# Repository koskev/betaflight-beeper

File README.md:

# bf-beeper

This is a small beeper board, which is designed to find a lost model aircraft.
It functions pretty much identical to the other commercial beepers.
The main feature is the ability to deactivate the beeper using Betaflight.

Just activate the normal beeper function of Betaflight and pull the battery.
Since the manual beep pattern is unique all other beep sources won't trigger the disarm.

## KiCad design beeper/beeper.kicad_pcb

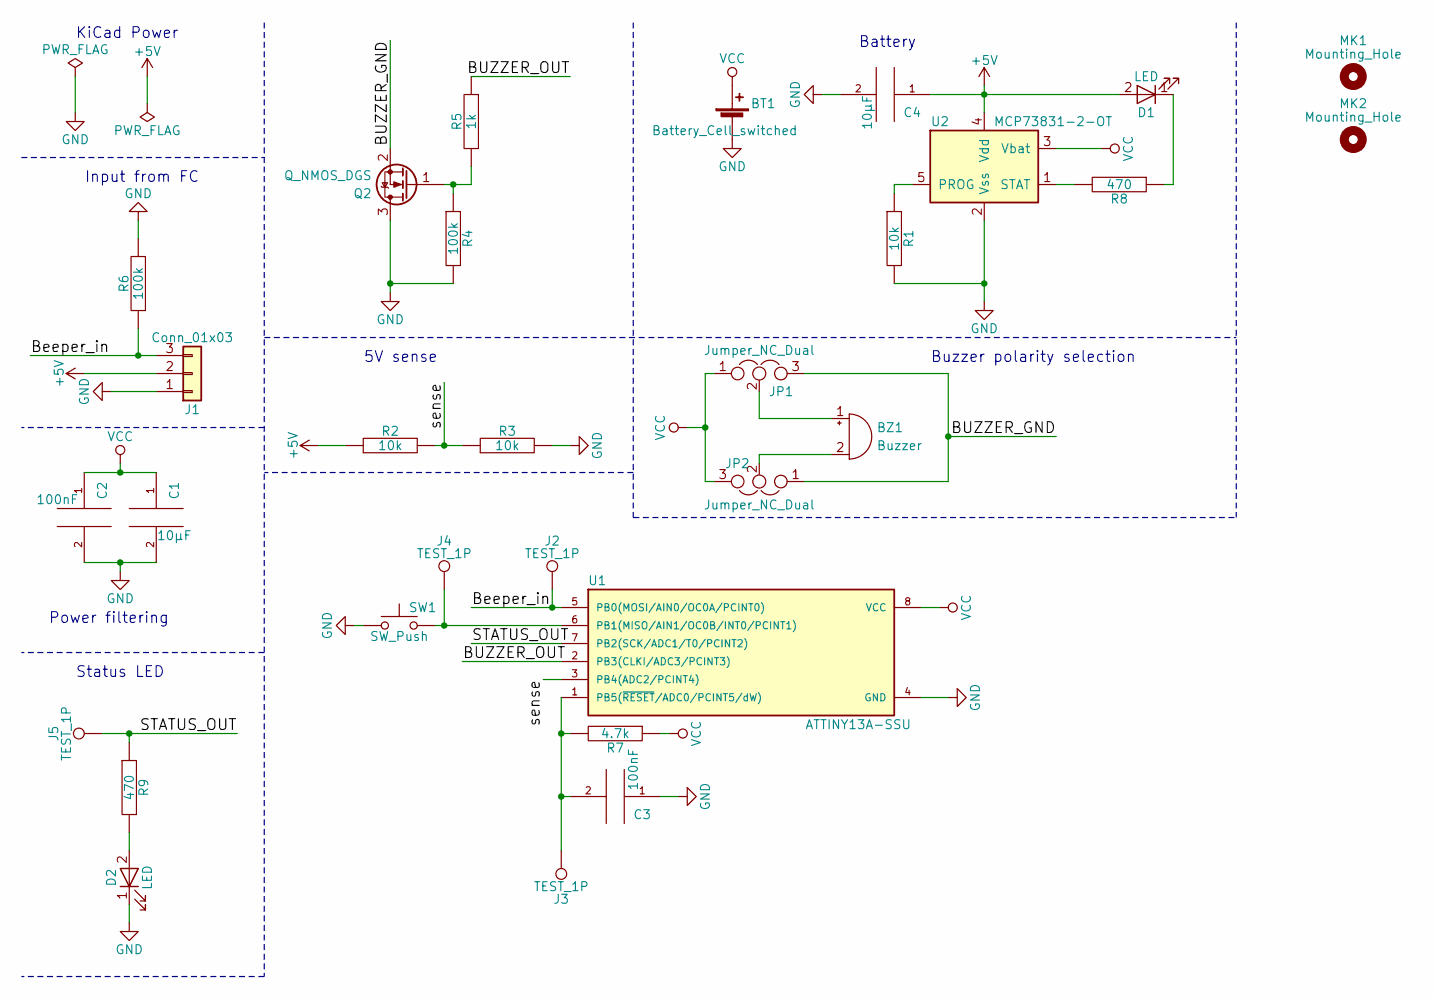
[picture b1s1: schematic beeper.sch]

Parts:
BT1: Battery_Cell_switched; PinHeader_2x01_P1.00mm_Vertical_SMD
BZ1: Buzzer; Buzzer_12x9.5RM7.6
C1, C4: 10µF; C_0805_2012Metric
C2, C3: 100nF; C_0603_1608Metric
D1, D2: LED; LED_0805_2012Metric_Castellated
J1: Conn_01x03; PinHeader_1x03_P2.54mm_Vertical
J2, J3, J4, J5: TEST_1P; TestPoint_Pad_D1.0mm
JP1, JP2: Jumper_NC_Dual; SolderJumper-3_P1.3mm_Open_RoundedPad1.0x1.5mm
MK1, MK2: Mounting_Hole; MountingHole_3.2mm_M3
Q2: Q_NMOS_DGS; SOT-23
R1, R2, R3: 10k; R_0805_2012Metric
R4, R6: 100k; R_0805_2012Metric
R5: 1k; R_0805_2012Metric
R7: 4.7k; R_0805_2012Metric
R8, R9: 470; R_0805_2012Metric
SW1: SW_Push; SW_SPST_CK_RS282G05A3
U1: ATTINY13A-SSU; SOIC-8_3.9x4.9mm_P1.27mm
U2: MCP73831-2-OT; SOT-23-5

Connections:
+5V: C4.1, D1.2 (A), J1.2, R2.1, U2.4 (Vdd)
/BUZZER_GND: JP1.3, JP2.1, Q2.2 (S)
/BUZZER_OUT: R5.2, U1.2 (PB3(CLKI/ADC3/PCINT3))
/Beeper_in: J1.3, J2.1, R6.1, U1.5 (PB0(MOSI/AIN0/OC0A/PCINT0))
/STATUS_OUT: J5.1, R9.1, U1.7 (PB2(SCK/ADC1/T0/PCINT2))
/sense: R2.2, R3.1, U1.3 (PB4(ADC2/PCINT4))
GND: BT1.1 (-), C1.2, C2.2, C3.1, C4.2, D2.1 (K), J1.1, Q2.3 (D), R1.2, R3.2, R4.2, R6.2, SW1.1, U1.4 (GND), U2.2 (Vss)
unnamed: BZ1.1 (-), JP1.2
unnamed: BZ1.2 (+), JP2.2
unnamed: C3.2, J3.1, R7.2, U1.1 (PB5(~RESET~/ADC0/PCINT5/dW))
unnamed: D1.1 (K), R8.1
unnamed: D2.2 (A), R9.2
unnamed: J4.1, SW1.2, U1.6 (PB1(MISO/AIN1/OC0B/INT0/PCINT1))
unnamed: Q2.1 (G), R4.1, R5.1
unnamed: R1.1, U2.5 (PROG)
unnamed: R8.2, U2.1 (STAT)
VCC: BT1.2 (+), C1.1, C2.1, JP1.1, JP2.3, R7.1, U1.8 (VCC), U2.3 (Vbat)

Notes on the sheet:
KiCad Power
Input from FC
Battery
Power filtering
5V sense
Status LED
Buzzer polarity selection

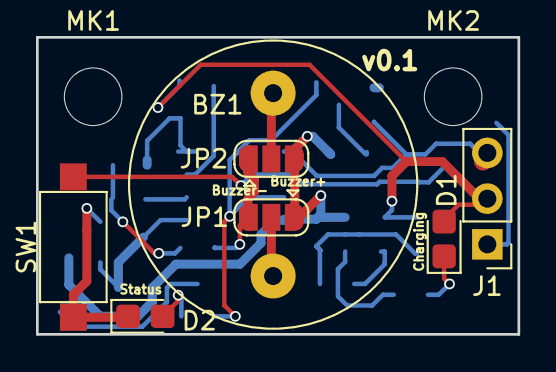
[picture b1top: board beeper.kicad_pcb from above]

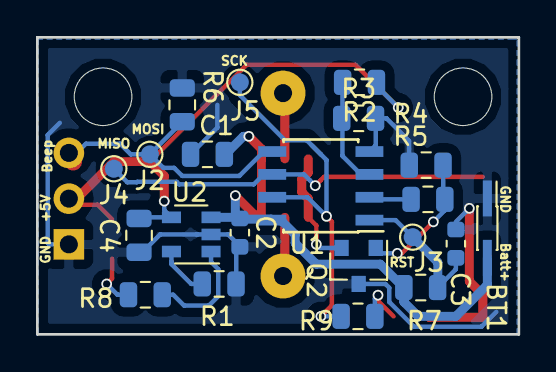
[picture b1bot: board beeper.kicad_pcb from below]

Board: 2 copper layers, 26.8 x 16.5 mm, 30 parts (21 on the bottom side), 17 nets.

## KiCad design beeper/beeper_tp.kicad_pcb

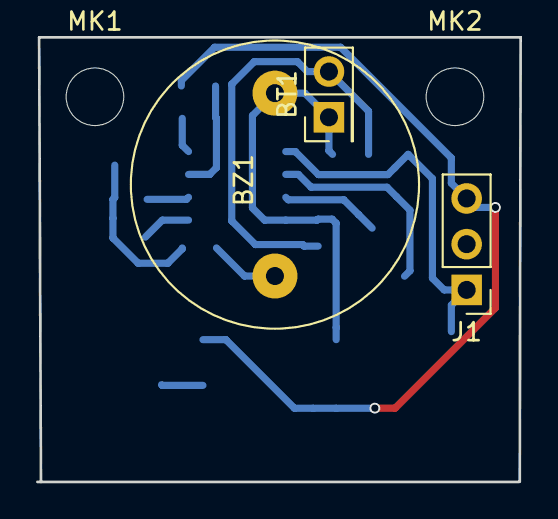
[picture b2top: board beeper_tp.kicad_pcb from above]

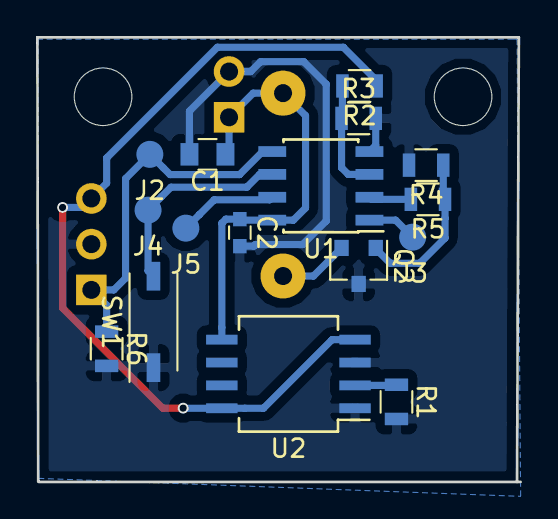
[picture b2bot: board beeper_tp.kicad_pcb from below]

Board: 2 copper layers, 26.8 x 24.7 mm, 21 parts (16 on the bottom side), 12 nets.

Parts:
BT1: Battery_Cell; Pin_Header_Straight_2x01_Pitch2.54mm
BZ1: Buzzer; BUZZER
C1: 10µF; C_0805
C2: 100nF; C_0603
J1: Conn_01x03; Pin_Header_Straight_1x03_Pitch2.54mm
J2, J3, J4, J5: TEST_1P; Measurement_Point_Round-SMD-Pad_Small
MK1, MK2: Mounting_Hole; MountingHole_3.2mm_M3
Q2: Q_NMOS_DGS; SOT-23
R1, R2, R3, R4, R5, R6: R; R_0805
SW1: SW_Push; SW_DIP_x1_W5.08mm_Slide_Copal_CHS-A
U1: ATTINY13A-SSU; SOIC-8_3.9x4.9mm_Pitch1.27mm
U2: TP4056; SO-8_5.3x6.2mm_Pitch1.27mm

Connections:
+5V: J1.3, R2.1, U2.4, U2.8
/Beeper_in: J1.1, J2.1, R6.1, U1.5
/sense: R2.2, R3.1, U1.3
GND: BT1.2, C1.2, C2.2, J1.2, Q2.3, R1.2, R3.2, R4.2, R6.2, SW1.1, U1.4, U2.1, U2.3
unnamed: BZ1.1, Q2.2
unnamed: J3.1, U1.1
unnamed: J4.1, SW1.2, U1.6
unnamed: J5.1, U1.7
unnamed: Q2.1, R4.1, R5.1
unnamed: R1.1, U2.2
unnamed: R5.2, U1.2
VCC: BT1.1, BZ1.2, C1.1, C2.1, U1.8, U2.5

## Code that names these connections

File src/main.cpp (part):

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
#define SENSE_DDR DDRB
#define SENSE_PORT PORTB
#define SENSE_PIN PB4

#define BEEPER_IN_DDR DDRB
#define BEEPER_IN_PORT PORTB
#define BEEPER_IN_PIN PB3

#define BEEPER_OUT_DDR DDRB
#define BEEPER_OUT_PORT PORTB
#define BEEPER_OUT_PIN PB0

#define BUTTON_DDR DDRB
#define BUTTON_PORT PORTB
#define BUTTON_PIN PB1

#define LED_DDR DDRB
#define LED_PORT PORTB
#define LED_PIN PB2

#define BEEP_PATTERN_SIZE 2
#define BEEP_PATTERN_NUM 2
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
STATIC_TEST bool is_beeper_input_set(){
#ifdef SIGNAL_ACTIVE_LOW
	return !(PINB & (1 << BEEPER_IN_PIN));
#else
	return PINB & (1 << BEEPER_IN_PIN);
#endif
}

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
	// pulldown not installed and signal inverted
#ifndef SIGNAL_ACTIVE_LOW
	BEEPER_IN_PORT &= ~(1 << BEEPER_IN_PIN);
#endif

	SENSE_PORT &= ~(1 << SENSE_PIN);
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
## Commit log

2024-02-13 PCB v0.2 final
2024-02-13 Final v0.2 (ordered)
2024-02-13 Add firmware.
2024-02-13 Version 2.
2024-02-13 PCB v0.2
2024-02-13 First version.
2024-02-13 Working firmware with passive buzzer.
2024-02-13 Update pcb info
2024-02-13 Set license to GPLv3
2024-02-13 Add makefile
2024-02-13 Enable setting the frequency at runtime.
